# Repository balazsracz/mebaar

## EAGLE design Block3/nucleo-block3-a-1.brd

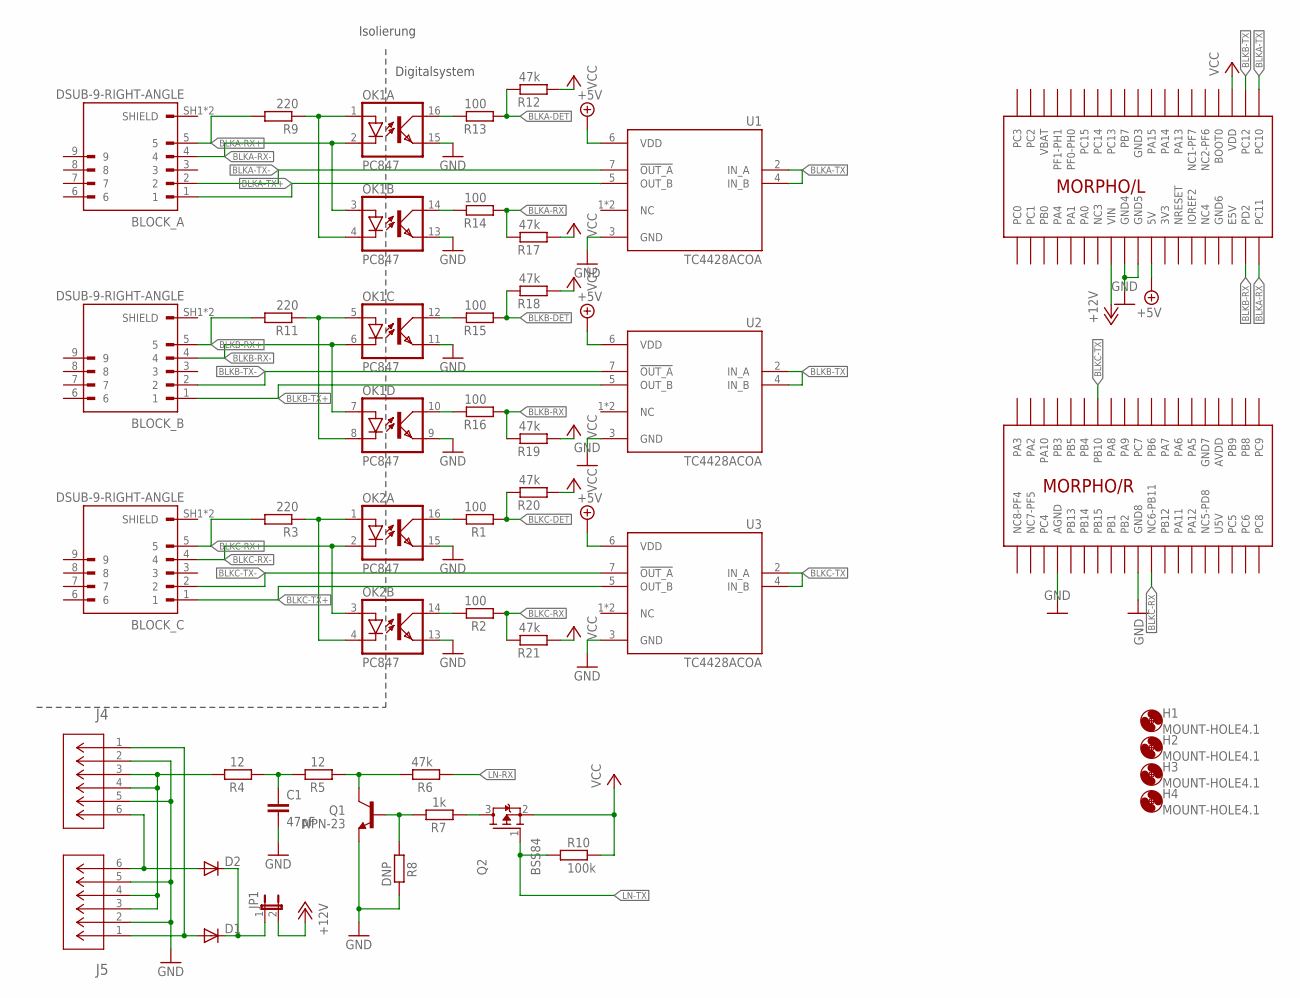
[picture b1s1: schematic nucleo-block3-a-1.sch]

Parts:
BLOCK_A: DSUB-9-RIGHT-ANGLE; ASSMANN_A-DS_09_A_KG-T2S
BLOCK_B: DSUB-9-RIGHT-ANGLE; ASSMANN_A-DS_09_A_KG-T2S
BLOCK_C: DSUB-9-RIGHT-ANGLE; ASSMANN_A-DS_09_A_KG-T2S
C1: 47pF; C0805
D1, D2: DIODEDO-214AA-NODOC; DO214AA-NODOC
G1: NUCLEO_64_GENERIC; NUCLEO_BRD_BASE64
H1, H2, H3, H4: MOUNT-HOLE4.1; 4,1
J4, J5: MODJACK6P6C-MJ3245-66-0CONN_MJ3245-66-0_GCT; CONN_MJ3245-66-0_GCT
JP1: JP1E; JP1
OK1, OK2: PC847; DIL16
Q1: NPN-23; SOT23
Q2: BSS84; SOT23-PCH
R1, R2, R13, R14, R15, R16: 100; R0805
R3, R9, R11: 220; R0805
R4, R5: 12; R0805
R6, R12, R17, R18, R19, R20, R21: 47k; R0805
R7: 1k; R0805
R8: DNP; R0805
R10: 100k; R0805
U1, U2, U3: TC4428ACOA; SOIC127P600X175-8N

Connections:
3V3: G1.3V3
+5V: G1.5V2 (5V), U1.6 (VDD), U2.6 (VDD), U3.6 (VDD)
+12V: G1.VIN2 (VIN), JP1.2
AVDD: G1.AVDD
BLKA-DET: R12.2, R13.1
BLKA-RX: G1.PC11, R14.1, R17.2
BLKA-RX+: BLOCK_A.5, R9.2
BLKA-RX-: BLOCK_A.4, OK1.2 (C), OK1.3 (A)
BLKA-TX: G1.PC10, U1.2 (IN_A), U1.4 (IN_B)
BLKA-TX+: BLOCK_A.1, U1.5 (OUT_B)
BLKA-TX-: BLOCK_A.2, U1.7 (!OUT_A)
BLKB-DET: R15.1, R18.2
BLKB-RX: G1.PD2, R16.1, R19.2
BLKB-RX+: BLOCK_B.5, R11.2
BLKB-RX-: BLOCK_B.4, OK1.6 (C), OK1.7 (A)
BLKB-TX: G1.PC12, U2.2 (IN_A), U2.4 (IN_B)
BLKB-TX+: BLOCK_B.1, U2.5 (OUT_B)
BLKB-TX-: BLOCK_B.2, U2.7 (!OUT_A)
BLKC-DET: R1.1, R20.2
BLKC-RX: G1.NC6-PB11, R2.1, R21.2
BLKC-RX+: BLOCK_C.5, R3.2
BLKC-RX-: BLOCK_C.4, OK2.2 (C), OK2.3 (A)
BLKC-TX: G1.PB10, U3.2 (IN_A), U3.4 (IN_B)
BLKC-TX+: BLOCK_C.1, U3.5 (OUT_B)
BLKC-TX-: BLOCK_C.2, U3.7 (!OUT_A)
E5V: G1.E5V
GND: C1.2, G1.AGND, G1.GND4, G1.GND5, G1.GND8, J4.2, J4.5, J5.2, J5.5, OK1.9 (EMIT), OK1.11 (EMIT), OK1.13 (EMIT), OK1.15 (EMIT), OK2.13 (EMIT), OK2.15 (EMIT), Q1.2 (E), R8.2, U1.3 (GND), U2.3 (GND), U3.3 (GND)
GND3: G1.GND3
GND6: G1.GND6
GND7: G1.GND7
LN-RX: R6.1
LN-TX: Q2.1 (G), R10.1
unnamed: OK2.1 (A), OK2.4 (C), R3.1
unnamed: OK2.16 (COL), R1.2
unnamed: OK2.14 (COL), R2.2
unnamed: D2.A, J4.6, J5.6
unnamed: C1.1, R4.1, R5.2
unnamed: D1.A, J4.1, J5.1
unnamed: J4.3, J4.4, J5.3, J5.4, R4.2
unnamed: D1.C, D2.C, JP1.1
unnamed: Q1.3 (C), R5.1, R6.2
unnamed: Q2.3 (D), R7.1
unnamed: Q1.1 (B), R7.2, R8.1
unnamed: OK1.1 (A), OK1.4 (C), R9.1
unnamed: OK1.5 (A), OK1.8 (C), R11.1
unnamed: OK1.16 (COL), R13.2
unnamed: OK1.14 (COL), R14.2
unnamed: OK1.12 (COL), R15.2
unnamed: OK1.10 (COL), R16.2
U5V: G1.U5V
VBAT: G1.VBAT
VCC: G1.VDD, Q2.2 (S), R10.2, R12.1, R17.1, R18.1, R19.1, R20.1, R21.1

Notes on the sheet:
Isolierung
Digitalsystem

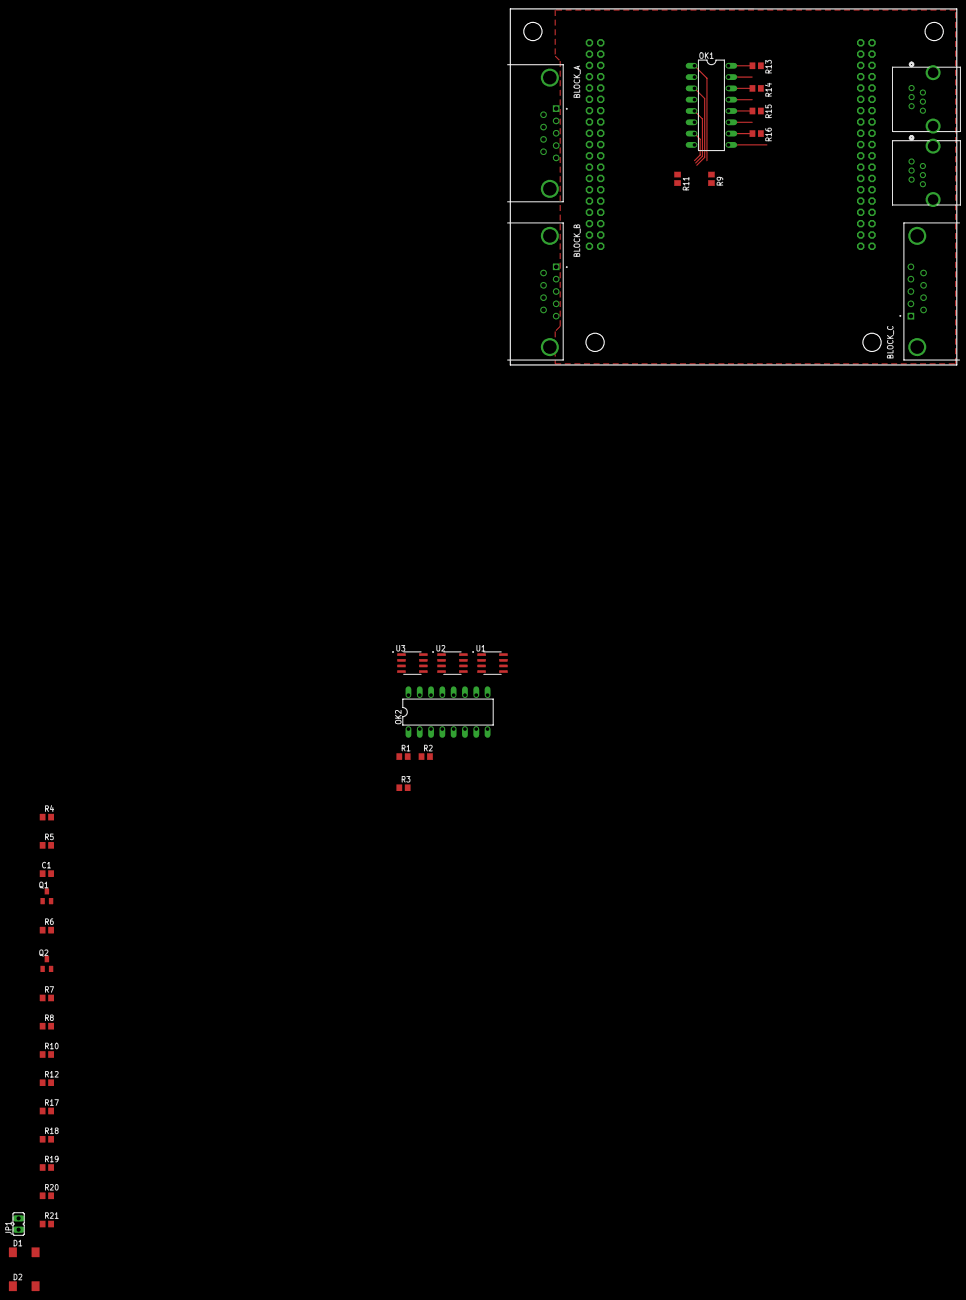
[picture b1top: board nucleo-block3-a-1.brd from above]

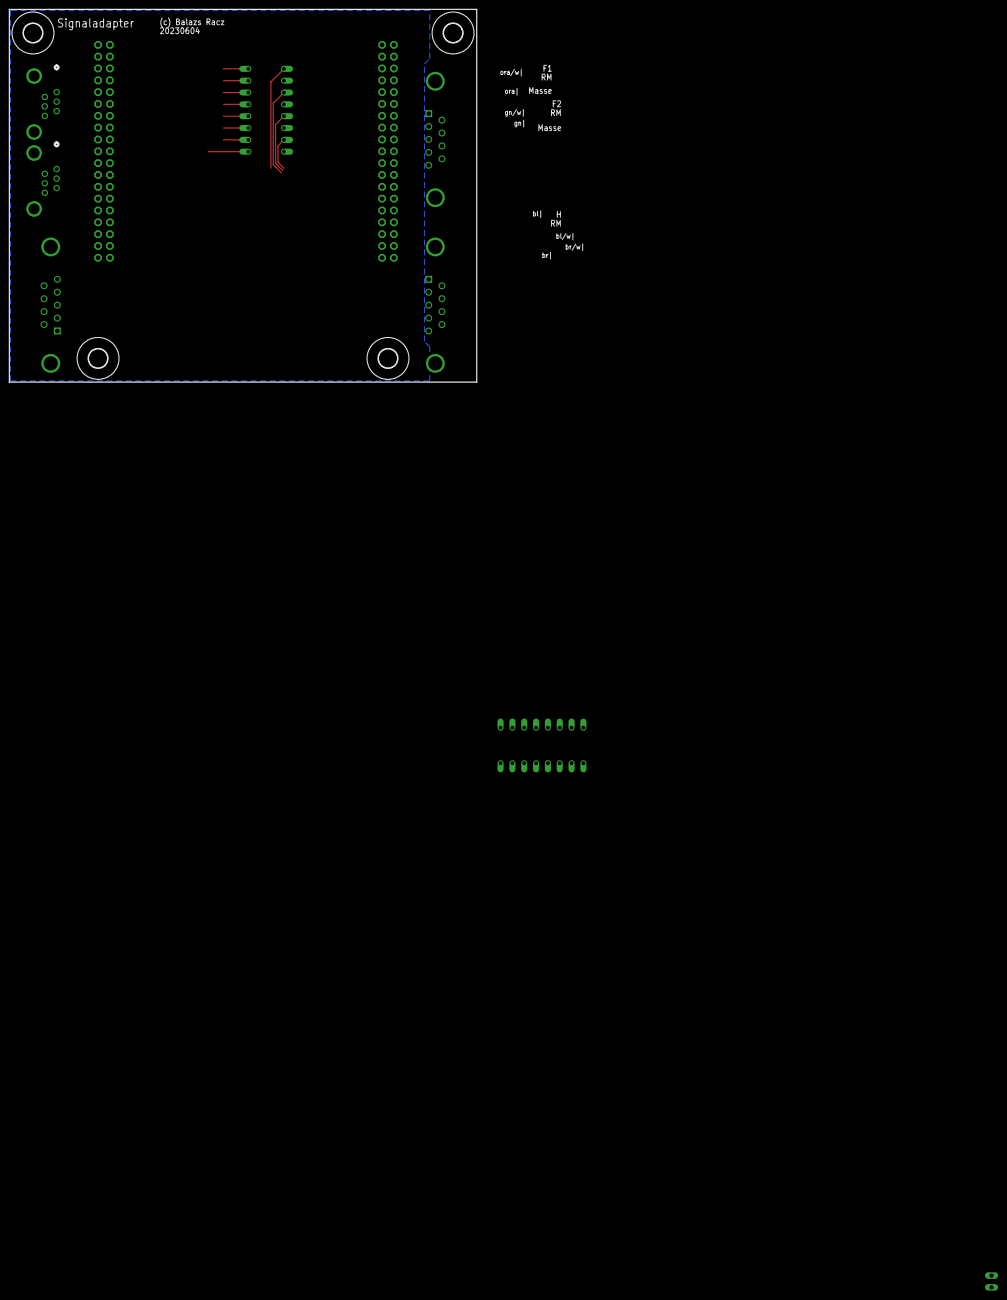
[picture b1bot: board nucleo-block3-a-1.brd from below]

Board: 2 copper layers, 100.3 x 80.0 mm, 42 parts (4 on the bottom side), 43 nets.

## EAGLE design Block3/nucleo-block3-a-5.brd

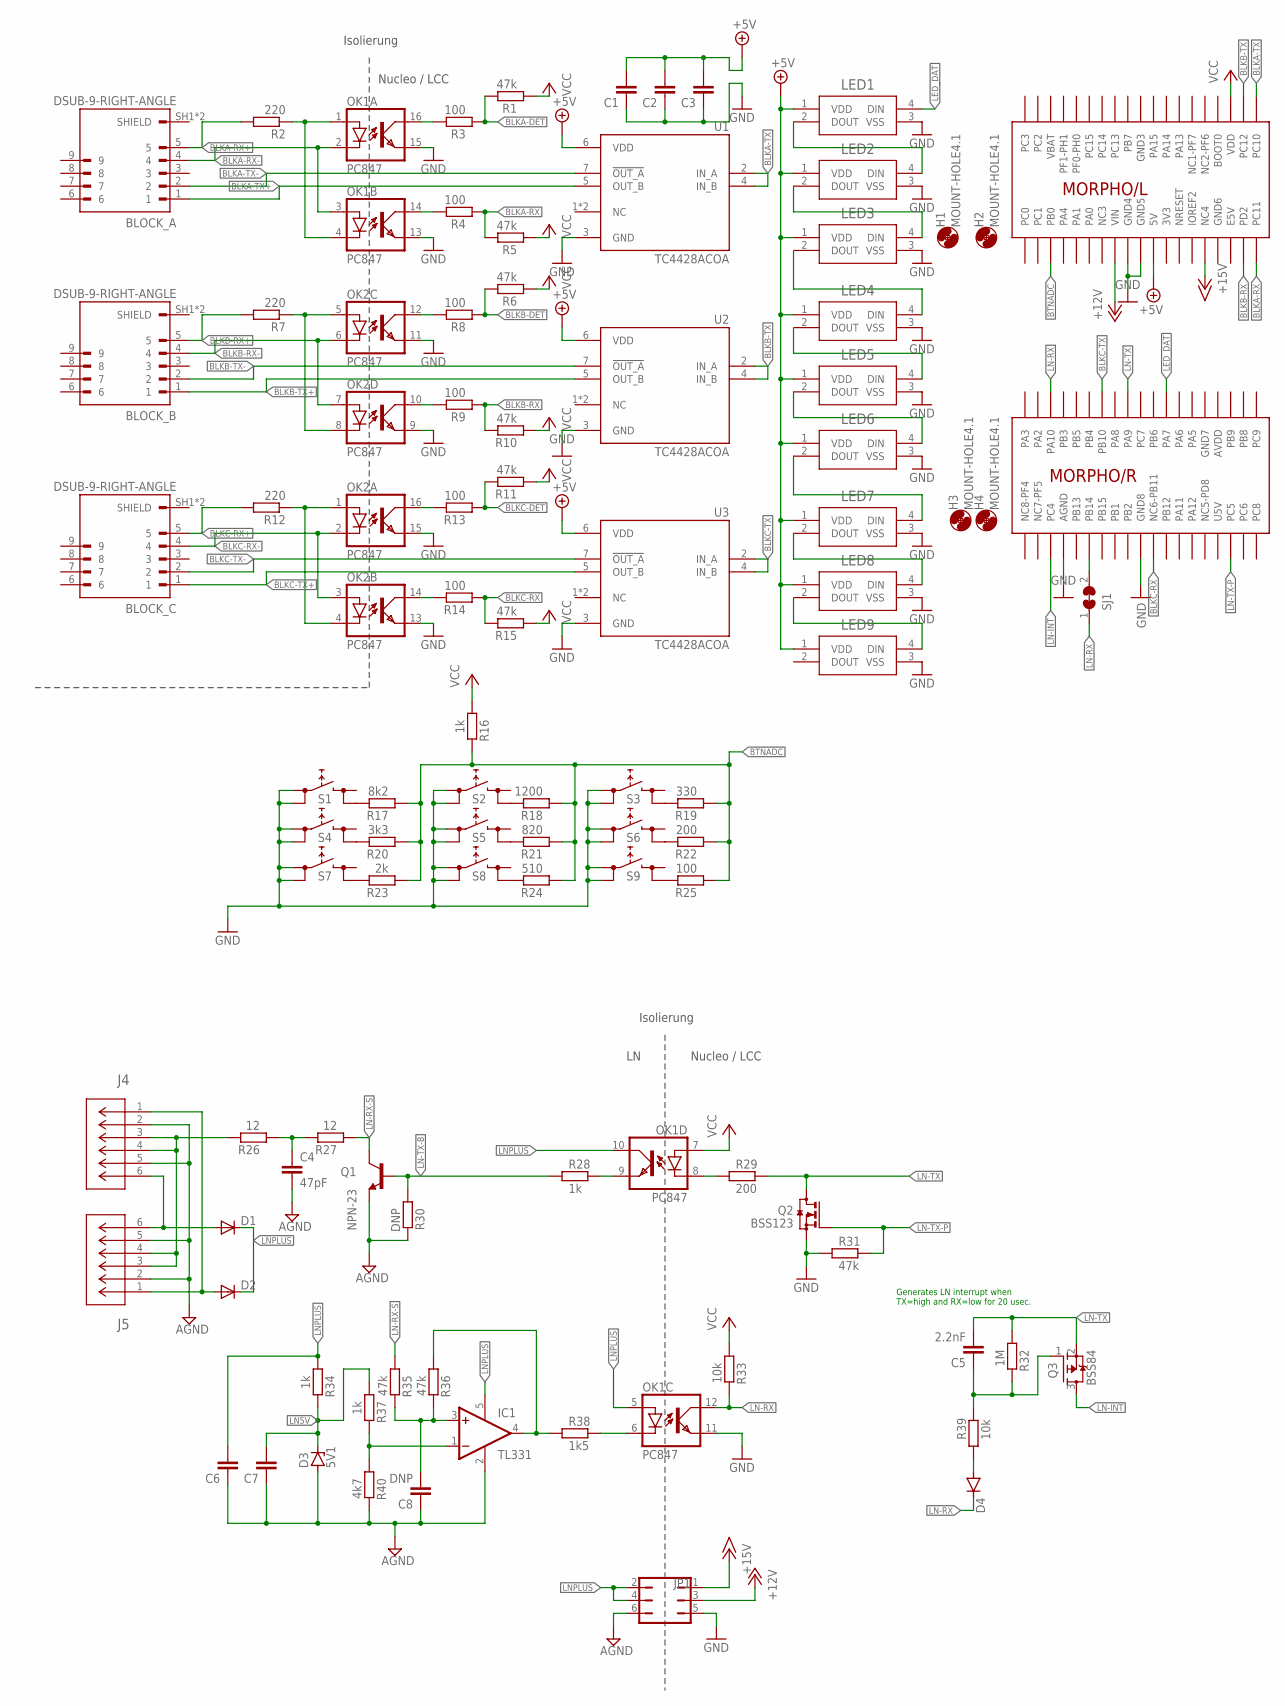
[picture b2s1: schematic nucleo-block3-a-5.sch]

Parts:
BLOCK_A: DSUB-9-RIGHT-ANGLE; ASSMANN_A-DS_09_A_KG-T2S
BLOCK_B: DSUB-9-RIGHT-ANGLE; ASSMANN_A-DS_09_A_KG-T2S
BLOCK_C: DSUB-9-RIGHT-ANGLE; ASSMANN_A-DS_09_A_KG-T2S
C1, C2, C3, C6, C7: C-EUC0805; C0805
C4: 47pF; C0805
C5: 2.2nF; C0805
C8: DNP; C0805
D1, D2: DIODEDO-214AA-NODOC; DO214AA-NODOC
D3: 5V1; SOD80C
D4: DIODE-MINIMELF; MINIMELF
G1: NUCLEO_64_GENERIC; NUCLEO_BRD_BASE64
H1, H2, H3, H4: MOUNT-HOLE4.1; 4,1
IC1: TL331; DBV-R-PDSO-G5
J4, J5: MODJACK6P6C-MJ3245-66-0CONN_MJ3245-66-0_GCT; CONN_MJ3245-66-0_GCT
JP1: JP3Q
LED1, LED2, LED3, LED4, LED5, LED6, LED7, LED8, LED9: LED-2812BCOM-16347_SPK-M; COM-16347_SPK-M
OK1, OK2: PC847; DIL16
Q1: NPN-23; SOT23
Q2: BSS123; SOT23-NCH
Q3: BSS84; SOT23-PCH
R1, R5, R6, R10, R11, R15, R31, R35, R36: 47k; R0805
R2, R7, R12: 220; R0805
R3, R4, R8, R9, R13, R14: 100; R0805
R16, R28, R34, R37: 1k; R0805
R17: 8k2; R0603
R18: 1200; R0603
R19: 330; R0603
R20: 3k3; R0603
R21: 820; R0603
R22: 200; R0603
R23: 2k; R0603
R24: 510; R0603
R25: 100; R0603
R26, R27: 12; R0805
R29: 200; R0805
R30: DNP; R0805
R32: 1M; R0805
R33, R39: 10k; R0805
R38: 1k5; R0805
R40: 4k7; R0805
S1, S2, S3, S4, S5, S6, S7, S8, S9: W1; TACTSW-6X6
SJ1: SJ-C; SJW-C
U1, U2, U3: TC4428ACOA; SOIC127P600X175-8N

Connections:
3V3: G1.3V3
+5V: C1.2, C2.2, C3.2, G1.5V2 (5V), LED1.1 (VDD), LED2.1 (VDD), LED3.1 (VDD), LED4.1 (VDD), LED5.1 (VDD), LED6.1 (VDD), LED7.1 (VDD), LED8.1 (VDD), LED9.1 (VDD), U1.6 (VDD), U2.6 (VDD), U3.6 (VDD)
+12V: G1.VIN2 (VIN), JP1.3
+15V: G1.NC4, JP1.1
AGND: C4.2, C6.1, C7.1, C8.1, D3.A, IC1.2 (GND), J4.2, J4.5, J5.2, J5.5, JP1.6, Q1.2 (E), R30.2, R40.2
AVDD: G1.AVDD
BLKA-DET: R1.2, R3.1
BLKA-RX: G1.PC11, R4.1, R5.2
BLKA-RX+: BLOCK_A.5, R2.2
BLKA-RX-: BLOCK_A.4, OK1.2 (C), OK1.3 (A)
BLKA-TX: G1.PC10, U1.2 (IN_A), U1.4 (IN_B)
BLKA-TX+: BLOCK_A.1, U1.5 (OUT_B)
BLKA-TX-: BLOCK_A.2, U1.7 (!OUT_A)
BLKB-DET: R6.2, R8.1
BLKB-RX: G1.PD2, R9.1, R10.2
BLKB-RX+: BLOCK_B.5, R7.2
BLKB-RX-: BLOCK_B.4, OK2.6 (C), OK2.7 (A)
BLKB-TX: G1.PC12, U2.2 (IN_A), U2.4 (IN_B)
BLKB-TX+: BLOCK_B.1, U2.5 (OUT_B)
BLKB-TX-: BLOCK_B.2, U2.7 (!OUT_A)
BLKC-DET: R11.2, R13.1
BLKC-RX: G1.NC6-PB11, R14.1, R15.2
BLKC-RX+: BLOCK_C.5, R12.2
BLKC-RX-: BLOCK_C.4, OK2.2 (C), OK2.3 (A)
BLKC-TX: G1.PB10, U3.2 (IN_A), U3.4 (IN_B)
BLKC-TX+: BLOCK_C.1, U3.5 (OUT_B)
BLKC-TX-: BLOCK_C.2, U3.7 (!OUT_A)
BTNADC: G1.PB0, R16.2, R17.1, R18.1, R19.1, R20.1, R21.1, R22.1, R23.1, R24.1, R25.1
E5V: G1.E5V
GND: C1.1, C2.1, C3.1, G1.AGND, G1.GND4, G1.GND5, G1.GND8, JP1.5, LED1.3 (VSS), LED2.3 (VSS), LED3.3 (VSS), LED4.3 (VSS), LED5.3 (VSS), LED6.3 (VSS), LED7.3 (VSS), LED8.3 (VSS), LED9.3 (VSS), OK1.11 (EMIT), OK1.13 (EMIT), OK1.15 (EMIT), OK2.9 (EMIT), OK2.11 (EMIT), OK2.13 (EMIT), OK2.15 (EMIT), Q2.2 (S), R31.1, S1.1 (1.1), S1.2 (1.2), S2.1 (1.1), S2.2 (1.2), S3.1 (1.1), S3.2 (1.2), S4.1 (1.1), S4.2 (1.2), S5.1 (1.1), S5.2 (1.2), S6.1 (1.1), S6.2 (1.2), S7.1 (1.1), S7.2 (1.2), S8.1 (1.1), S8.2 (1.2), S9.1 (1.1), S9.2 (1.2), U1.3 (GND), U2.3 (GND), U3.3 (GND)
GND3: G1.GND3
GND6: G1.GND6
GND7: G1.GND7
LED_DAT: G1.PA7, LED1.4 (DIN)
LN5V: C7.2, D3.C, R34.2, R37.1
LN-INT: G1.PC4, Q3.3 (D)
LN-RX: D4.C, G1.PA10, OK1.12 (COL), R33.2, SJ1.1
LN-RX-S: Q1.3 (C), R27.1, R35.1
LN-TX: C5.2, G1.PA9, Q2.3 (D), Q3.2 (S), R29.2, R32.1
LN-TX-B: Q1.1 (B), R28.1, R30.1
LN-TX-P: G1.PC5, Q2.1 (G), R31.2
LNPLUS: C6.2, D1.C, D2.C, IC1.5 (V+), JP1.2, JP1.4, OK1.5 (A), OK1.10 (COL), R34.1
unnamed: OK2.1 (A), OK2.4 (C), R12.1
unnamed: OK2.16 (COL), R13.2
unnamed: OK2.14 (COL), R14.2
unnamed: D1.A, J4.6, J5.6
unnamed: C4.1, R26.1, R27.2
unnamed: D2.A, J4.1, J5.1
unnamed: J4.3, J4.4, J5.3, J5.4, R26.2
unnamed: R17.2, S1.4 (2.2)
unnamed: D4.A, R39.1
unnamed: OK1.9 (EMIT), R28.2
unnamed: LED1.2 (DOUT), LED2.4 (DIN)
unnamed: LED2.2 (DOUT), LED3.4 (DIN)
unnamed: LED3.2 (DOUT), LED4.4 (DIN)
unnamed: LED4.2 (DOUT), LED5.4 (DIN)
unnamed: LED5.2 (DOUT), LED6.4 (DIN)
unnamed: LED6.2 (DOUT), LED7.4 (DIN)
unnamed: LED7.2 (DOUT), LED8.4 (DIN)
unnamed: LED8.2 (DOUT), LED9.4 (DIN)
unnamed: G1.PB14, SJ1.2
unnamed: R20.2, S4.4 (2.2)
unnamed: C5.1, Q3.1 (G), R32.2, R39.2
unnamed: R23.2, S7.4 (2.2)
unnamed: R18.2, S2.4 (2.2)
unnamed: R21.2, S5.4 (2.2)
unnamed: R24.2, S8.4 (2.2)
unnamed: IC1.1 (-IN), R37.2, R40.1
unnamed: C8.2, IC1.3 (+IN), R35.2, R36.2
unnamed: OK1.1 (A), OK1.4 (C), R2.1
unnamed: R19.2, S3.4 (2.2)
unnamed: R22.2, S6.4 (2.2)
unnamed: R25.2, S9.4 (2.2)
unnamed: OK2.5 (A), OK2.8 (C), R7.1
unnamed: IC1.4 (OUT), R36.1, R38.1
unnamed: OK1.8 (C), R29.1
unnamed: OK1.6 (C), R38.2
unnamed: OK1.16 (COL), R3.2
unnamed: OK1.14 (COL), R4.2
unnamed: OK2.12 (COL), R8.2
unnamed: OK2.10 (COL), R9.2
U5V: G1.U5V
VBAT: G1.VBAT
VCC: G1.VDD, OK1.7 (A), R1.1, R5.1, R6.1, R10.1, R11.1, R15.1, R16.1, R33.1

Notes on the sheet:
Isolierung
Nucleo / LCC
Generates LN interrupt when TX=high and RX=low for 20 usec.

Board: 2 copper layers, 91 parts (4 on the bottom side), 76 nets, no tracks yet.

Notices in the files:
Block3/nucleo-block3-a-1.sch:
LICENSE: Licensed by the Solderpad Hardware License V2.0
parts and their libraries:
COPYRIGHT: Copyright (C) 2024 Ultra Librarian. All rights reserved.
